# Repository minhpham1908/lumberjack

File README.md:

# Lumberjack - Through-hole ortholinear 60% keyboard PCB

Lumberjack is a split 5x12 ortholinear keyboard PCB using through-hole components only.

The goal of this project is to build an all through-hole component ortholinear PCB that fits in a standard 60% tray mount case.

Inspired by the [Plaid keyboard](https://github.com/hsgw/plaid).

* Designed to be easy to build with minimal soldering experience.
* All through-hole components, no SMD soldering required.
* Get that visible component aesthetic in a standard 60% tray-mount case.
* Supports both USB Mini and USB-C.
* Plateless or with FR4 switch plates.

# Ordering parts

See the [Bill of materials](BOM.md) for a detailed list of the required parts.

PCBs can be manufactuered by a variety of online PCB fabricators. You can use [PCBShopper](https://pcbshopper.com/) to search for the best price.

The zip file in the gerber directory contains the gerber files your fabricator will need to make the PCB [lumberjack.zip](https://github.com/peej/lumberjack-keyboard/blob/master/gerber/lumberjack.zip) PCB.

When uploading the gerber zip files, use the default PCB settings.

If you want to use a plate, there are gerbers for an FR4 plate. You will need two plates, one for each half of the keyboard.

# Construction

Solder all the components onto the top side of the PCB except the USB connector which should be on the back of the board. Leave the larger components until last so that the board will lie flat upsidedown while you solder the resistors and capacitors.

Take care to put the correct value resistors and capacitors in the correct places, the values are written on the silkmask along with the component reference. If you are unsure about the value of a resistor, check it with a multimeter.

Ensure that polarised components (diodes, LEDs, electrolytic capacitor (C3), IC socket) are in the correct orientation. The square pad is for the negative side of the component; for a diode this means the side with the black stripe; for LEDs and C3 the short leg is the cathode and goes in the square pad.

See [the build guide](guide.md) for more information.

# Firmware

Firmware is available in the QMK repository under the name `peej/lumberjack`.

Follow the [QMK firmware instructions](https://beta.docs.qmk.fm/using-qmk/guides/flashing/flashing) to build and flash the firmware.

To put the board into bootloader mode so it is ready to recieve firmware, press and hold the BOOT button (SW2) while pressing and releasing the RESET button (SW1). The board will now be detected as an USBasp device and can have the firmware flashed via the USB port.

Pressing the RESET button (SW1) on its own will restart the microprocessor. Once flashed with firmware it is neccessary to reset the keyboard so as to return control to the new firmware.

Note that due to the BOOT button (SW2) sharing a pin with column 3, when pressed the keys in that column will also activate. This is expected behavour but can be a little annoying or confusing if you are not expecting it.

## VIA

There is a VIA compatible firmware available in QMK. With this firmware flashed, the board will be automatically recognised by VIA when you plug it in.

## Bootloader

If you have a "raw" chip without a bootloader, you will need to compile and flash the bootloader onto the chip via another device. [See the build guide for more information](guide.md#bootloader).

## Matrix information

If you are building your own firmware, the following matrix information will be useful to you:

| Configuration   | Value                                  |
|-----------------|----------------------------------------|
| MATRIX_ROWS     | 6                                      |
| MATRIX_COLS     | 10                                     |
| MATRIX_ROW_PINS | C0, B5, B4, B3, B2, B1                 |
| MATRIX_COL_PINS | B0, D7, D6, D5, D4, D1, D0, C1, C2, C3 |
| DIODE_DIRECTION | COL2ROW                                |

Due to the limited pin number of the ATMEGA328P, the PCB uses a 6 by 10 matrix (16 pins) instead of a 5 by 12 matrix (17 pins), this makes organising the matrix in your firmware slightly more complicated. The image below shows pins for each key.

# Component cover

Cut a piece of 2mm thick acrylic to size (95x57mm) and drill 4 m2 holes in the corners for the standoffs. Use the PCB or cover.dxf as a guide for the hole positions, you can also use cover.dxf for laser cutting the correct size acrylic.

Affix the 4 standoffs to the PCB with screws from underneath the PCB. Use the remaining 4 screws to attach the acrylic to the top of the standoffs.

# Revisions

## Rev 1.1

* Fix cosmetic errors in silkscreen
* Increase resistor footprint size
* Fix R1 resistor connection to D-

## Rev 1.2

* Add JST socket footprint for USB daughterboard
* Rotate central mount hole 90 degrees

## Rev 1.3

* Add hybrid USB port footprint for mini and type C
* Fix numbering of zener diode footprints
* Flip MX7 to be south facing

## Rev 1.4

* Use USB footprint with better positioning
* Move 5.1k resistors to better location
* Change MX8 to allow both north and south facing switch
## Rev 1.5

* Change board outline to include cutouts for Bakeneko 60
* Re-route traces away from edges of the board
* Add through-hole JST connector footprint
* Add silkscreen art to underside

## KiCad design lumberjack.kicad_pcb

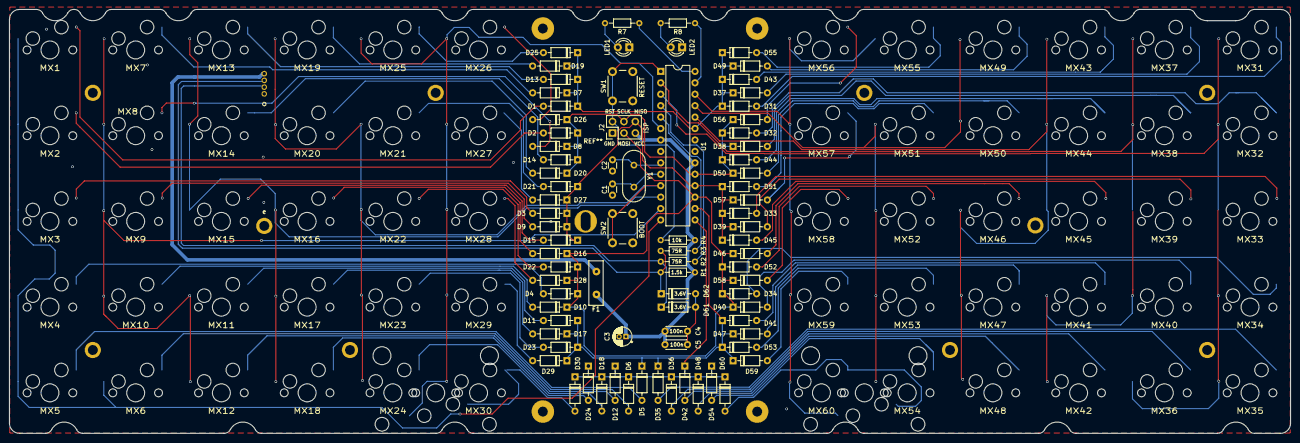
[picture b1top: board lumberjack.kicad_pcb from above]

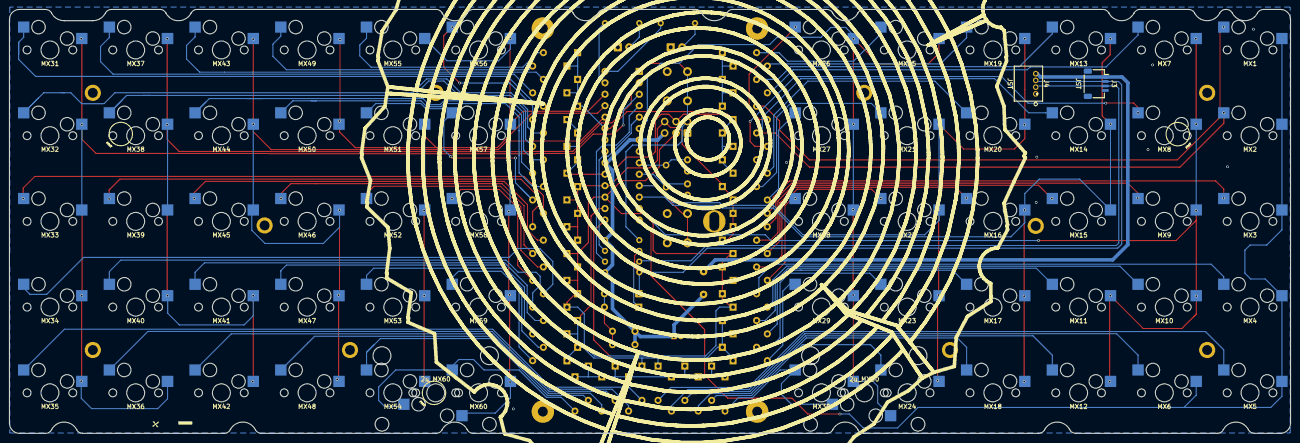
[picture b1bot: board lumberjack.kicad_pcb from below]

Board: 2 copper layers, 284.7 x 94.2 mm, 153 parts (2 on the bottom side), 90 nets.

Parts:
2u_MX30, 2u_MX60: SW_Push; MXOnly-2U-Hotswap
C1, C2: 22p; C_Disc_D3.0mm_W1.6mm_P2.50mm
C3: 4.7u; CP_Radial_D4.0mm_P1.50mm
C4, C5: 100n; C_Disc_D4.3mm_W1.9mm_P5.00mm
D1, D2, D3, D4, D5, D6, D7, D8, D9, D10, D11, D12, D13, D14, D15, D16, D17, D18, D19, D20, D21, D22, D23, D24, D25, D26, D27, D28, D29, D30, D31, D32, D33, D34, D35, D36, D37, D38, D39, D40, D41, D42, D43, D44, D45, D46, D47, D48, D49, D50, D51, D52, D53, D54, D55, D56, D57, D58, D59, D60: 1N4148; D_DO-35_SOD27_P7.62mm_Horizontal
D61, D62: 3.6V; D_DO-35_SOD27_P7.62mm_Horizontal
F1: 100mA; Fuse_Bourns_MF-RHT100
H1, H2, H3, H4: M2; MountingHole_M2
H5, H6, H7: M2; MountingSlot_M2
J2: AVR_ISP_6; PinHeader_2x03_P2.54mm_Vertical
J3: JST; JST_SH_SM04B-SRSS-TB_1x04-1MP_P1.00mm_Horizontal
J4: JST; S4B-ZRLFSN
LED1: RED; LED_D3.0mm
LED2: GREEN; LED_D3.0mm
MX1, MX2, MX3, MX4, MX5, MX6, MX7, MX8, MX9, MX10, MX11, MX12, MX13, MX14, MX15, MX16, MX17, MX18, MX19, MX20, MX21, MX22, MX23, MX24, MX25, MX26, MX27, MX28, MX29, MX30, MX31, MX32, MX33, MX34, MX35, MX36, MX37, MX38, MX39, MX40, MX41, MX42, MX43, MX44, MX45, MX46, MX47, MX48, MX49, MX50, MX51, MX52, MX53, MX54, MX55, MX56, MX57, MX58, MX59, MX60: SW_Push; MXOnly-1U-Hotswap
R1, R7, R8: 1.5k; R_Axial_DIN0204_L3.6mm_D1.6mm_P7.62mm_Horizontal
R2, R3: 75R; R_Axial_DIN0204_L3.6mm_D1.6mm_P7.62mm_Horizontal
R4: 10k; R_Axial_DIN0204_L3.6mm_D1.6mm_P7.62mm_Horizontal
SW1: RESET; SW_PUSH_6mm
SW2: BOOT; SW_PUSH_6mm
U1: ATMEGA328-PU; DIP-28_W7.62mm
Y1: 16MHz; Crystal_HC49-4H_Vertical
e: MountingHole_2.2mm_M2

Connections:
+5V: C3.1, C4.1, C5.1, F1.2, J2.5, R1.2, R4.1, U1.7, U1.20
/COL0: MX1.2, MX2.2, MX3.2, MX4.2, MX5.2, MX6.2, U1.14
/COL1: MX7.2, MX8.2, MX9.2, MX10.2, MX11.2, MX12.2, U1.13
/COL2: MX13.2, MX14.2, MX15.2, MX16.2, MX17.2, MX18.2, U1.12
/COL3: MX19.2, MX20.2, MX21.2, MX22.2, MX23.2, MX24.2, SW2.1, U1.11
/COL4: 2u_MX30.2, MX25.2, MX26.2, MX27.2, MX28.2, MX29.2, MX30.2, U1.6
/COL5: MX31.2, MX32.2, MX33.2, MX34.2, MX35.2, MX36.2, U1.3
/COL6: MX37.2, MX38.2, MX39.2, MX40.2, MX41.2, MX42.2, U1.2
/COL7: MX43.2, MX44.2, MX45.2, MX46.2, MX47.2, MX48.2, U1.24
/COL8: MX49.2, MX50.2, MX51.2, MX52.2, MX53.2, MX54.2, U1.25
/COL9: 2u_MX60.2, MX55.2, MX56.2, MX57.2, MX58.2, MX59.2, MX60.2, U1.26
/LED1: R7.1, U1.28
/LED2: R8.1, U1.27
/RESET: J2.2, R4.2, SW1.1, U1.1
/ROW0: D1.1, D7.1, D13.1, D19.1, D25.1, D31.1, D37.1, D43.1, D49.1, D55.1, U1.23
/ROW1: D2.1, D8.1, D14.1, D20.1, D26.1, D32.1, D38.1, D44.1, D50.1, D56.1, J2.4, U1.19
/ROW2: D3.1, D9.1, D15.1, D21.1, D27.1, D33.1, D39.1, D45.1, D51.1, D57.1, J2.6, U1.18
/ROW3: D4.1, D10.1, D16.1, D22.1, D28.1, D34.1, D40.1, D46.1, D52.1, D58.1, J2.3, U1.17
/ROW4: D5.1, D11.1, D17.1, D23.1, D29.1, D35.1, D41.1, D47.1, D53.1, D59.1, U1.16
/ROW5: D6.1, D12.1, D18.1, D24.1, D30.1, D36.1, D42.1, D48.1, D54.1, D60.1, U1.15
/USB_D+: R2.2, U1.4
/USB_D-: R3.2, U1.5
GND: C1.2, C2.2, C3.2, C4.2, C5.2, D61.2, D62.2, J2.1, J3.4, J4.1, LED1.1, LED2.1, SW1.2, SW2.2, U1.8, U1.22
unnamed: 2u_MX30.1, D30.2, MX30.1
unnamed: 2u_MX60.1, D60.2, MX60.1
unnamed: C1.1, U1.10, Y1.2
unnamed: C2.1, U1.9, Y1.1
unnamed: D1.2, MX1.1
unnamed: D2.2, MX2.1
unnamed: D3.2, MX3.1
unnamed: D4.2, MX4.1
unnamed: D5.2, MX5.1
unnamed: D6.2, MX6.1
unnamed: D7.2, MX7.1
unnamed: D8.2, MX8.1
unnamed: D9.2, MX9.1
unnamed: D10.2, MX10.1
unnamed: D11.2, MX11.1
unnamed: D12.2, MX12.1
unnamed: D13.2, MX13.1
unnamed: D14.2, MX14.1
unnamed: D15.2, MX15.1
unnamed: D16.2, MX16.1
unnamed: D17.2, MX17.1
unnamed: D18.2, MX18.1
unnamed: D19.2, MX19.1
unnamed: D20.2, MX20.1
unnamed: D21.2, MX21.1
unnamed: D22.2, MX22.1
unnamed: D23.2, MX23.1
unnamed: D24.2, MX24.1
unnamed: D25.2, MX25.1
unnamed: D26.2, MX26.1
unnamed: D27.2, MX27.1
unnamed: D28.2, MX28.1
unnamed: D29.2, MX29.1
unnamed: D31.2, MX31.1
unnamed: D32.2, MX32.1
unnamed: D33.2, MX33.1
unnamed: D34.2, MX34.1
unnamed: D35.2, MX35.1
unnamed: D36.2, MX36.1
unnamed: D37.2, MX37.1
unnamed: D38.2, MX38.1
unnamed: D39.2, MX39.1
unnamed: D40.2, MX40.1
unnamed: D41.2, MX41.1
unnamed: D42.2, MX42.1
unnamed: D43.2, MX43.1
unnamed: D44.2, MX44.1
unnamed: D45.2, MX45.1
unnamed: D46.2, MX46.1
unnamed: D47.2, MX47.1
unnamed: D48.2, MX48.1
unnamed: D49.2, MX49.1
unnamed: D50.2, MX50.1
unnamed: D51.2, MX51.1
unnamed: D52.2, MX52.1
unnamed: D53.2, MX53.1
unnamed: D54.2, MX54.1
unnamed: D55.2, MX55.1
unnamed: D56.2, MX56.1
unnamed: D57.2, MX57.1
unnamed: D58.2, MX58.1
unnamed: D59.2, MX59.1
unnamed: D61.1, J3.3, J4.2, R2.1
unnamed: D62.1, J3.2, J4.3, R1.1, R3.1
unnamed: F1.1, J3.1, J4.4
unnamed: LED1.2, R7.2
unnamed: LED2.2, R8.2

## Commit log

2021-12-01 edit for meow
2021-12-01 update gerber
2021-12-01 update plate
2021-12-03 Mod hotswap and clean sthg
    For meow60 keyboard compatible reason. I delete all thing related to usb to keep all switch only 1 way facing
    Change footprint to HS and mimic the wire in pcb (cause i like it!)
2021-12-09 Done wiring
2021-12-10 Add screw for oring and plate hole

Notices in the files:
parts and their libraries:
Copyright 2021 Accelerated Designs. All rights reserved.
